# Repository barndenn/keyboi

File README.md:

# MacroPad Concept 
This is my experimental Macropad to test certain features before scaling up. 

Features Included: 
- USB Type-C Connector 
- Bluetooth 
- Battery holder and onboard charging circuit
- OLED Battery Level Display
- Volume Knobs

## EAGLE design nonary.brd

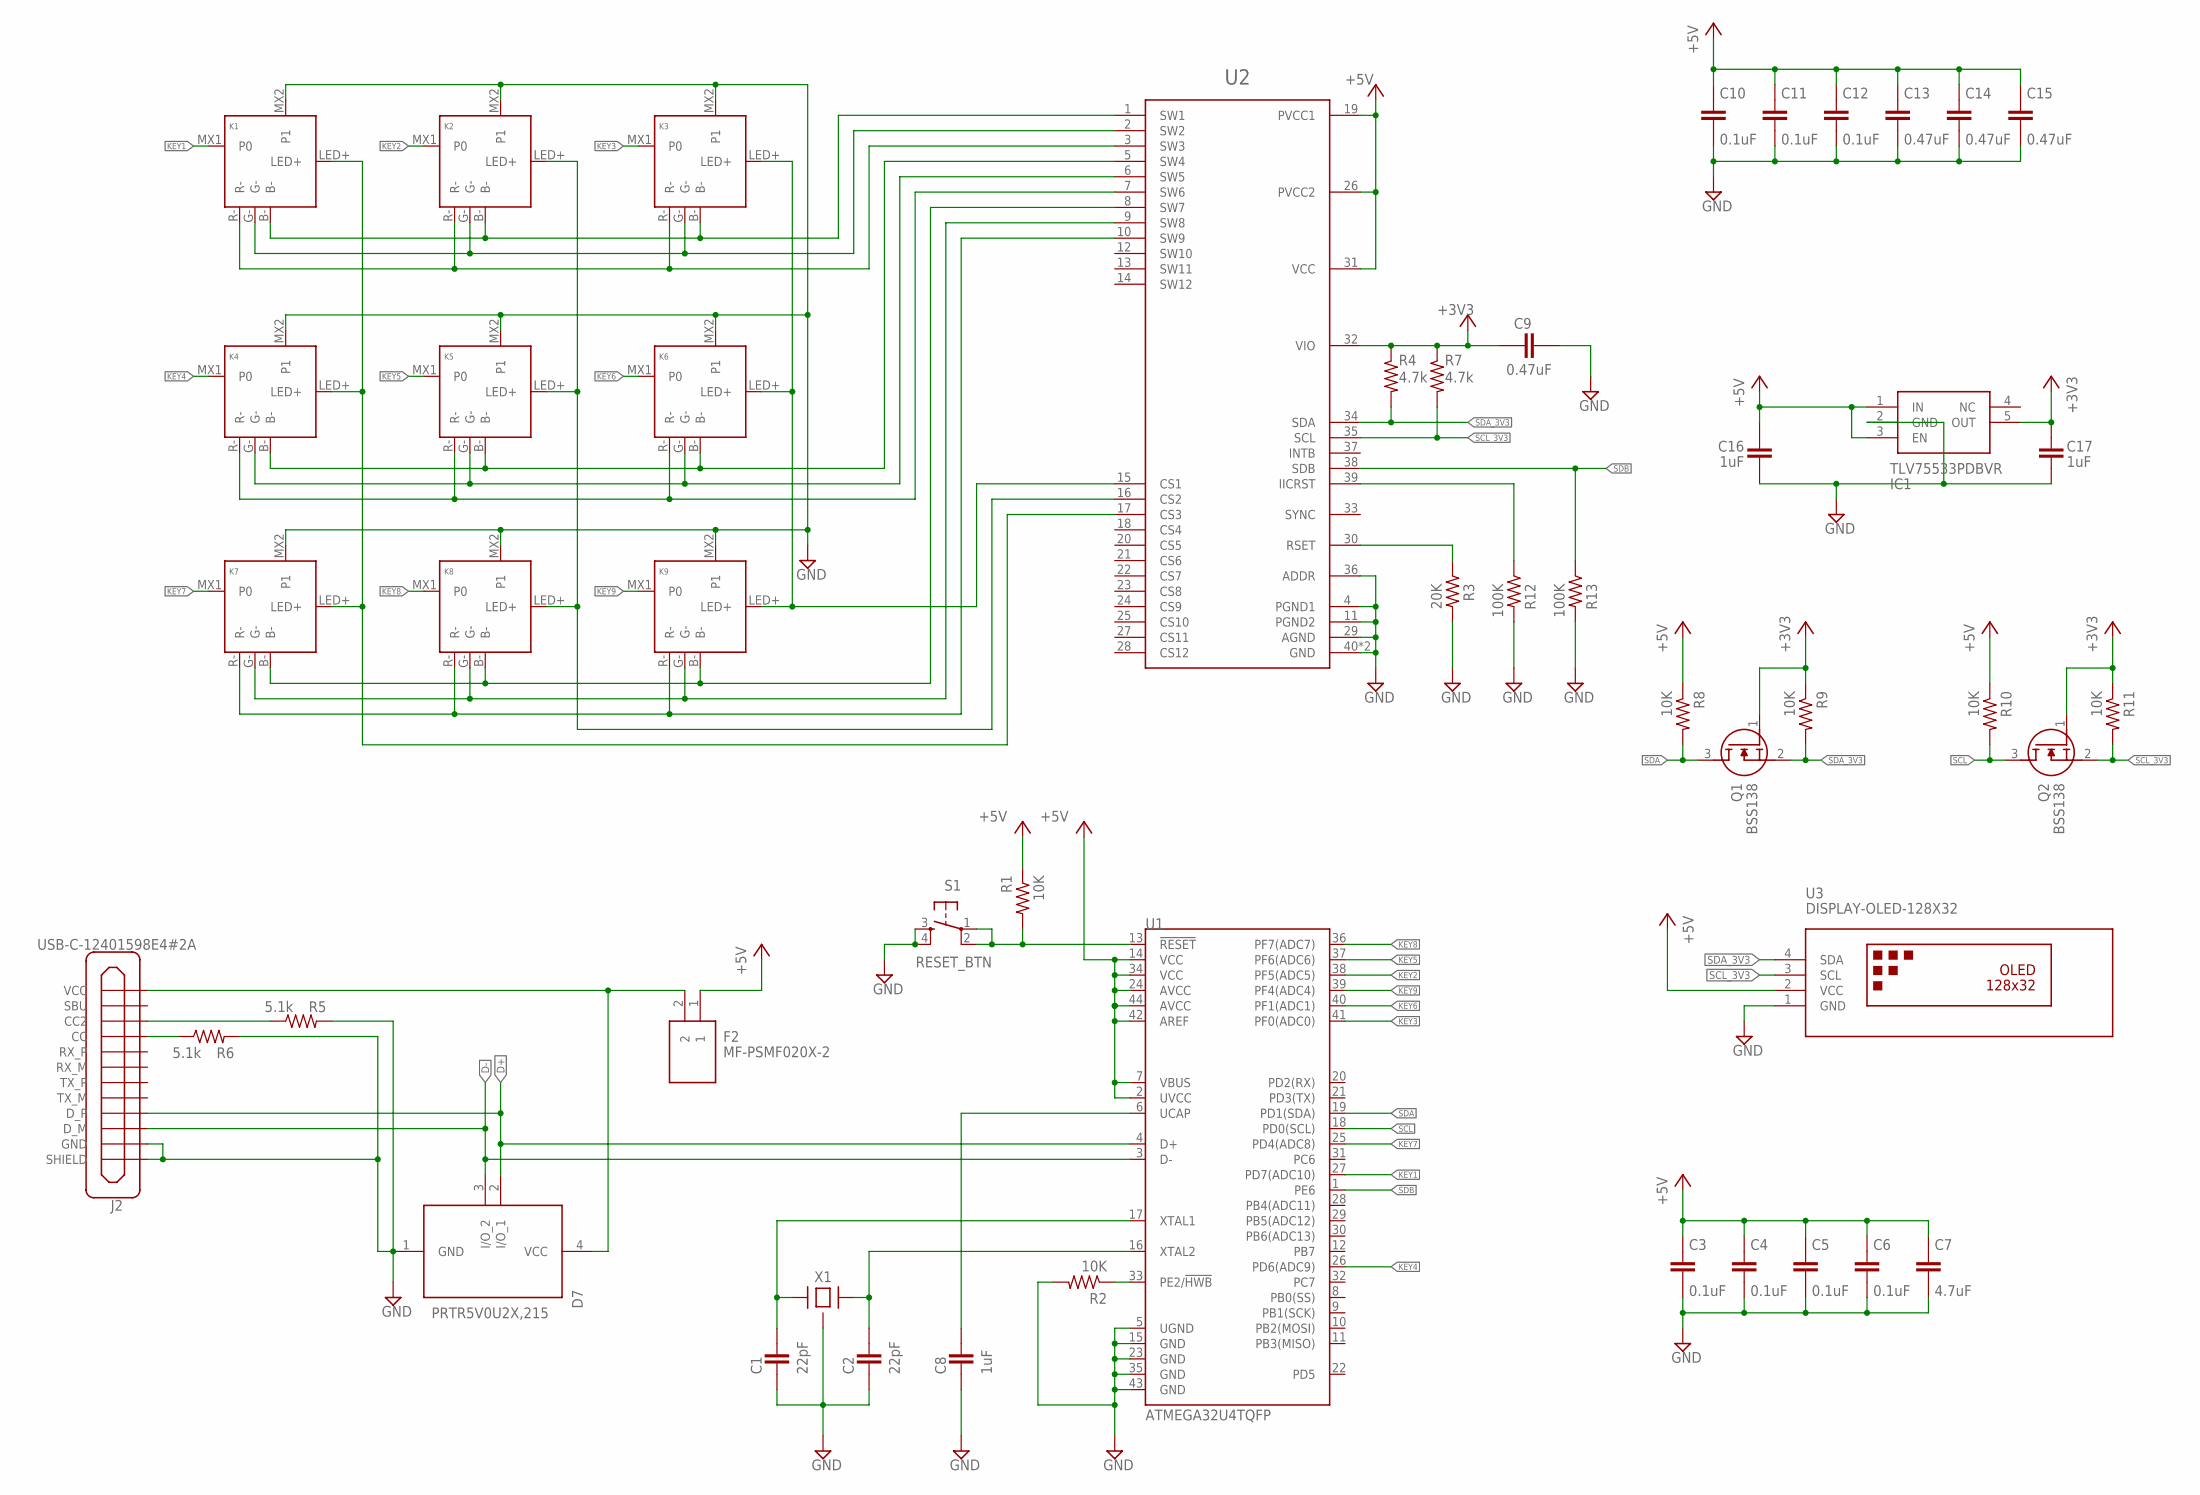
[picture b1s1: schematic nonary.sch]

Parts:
C1, C2: 22pF; C0603
C3, C4, C5, C6, C10, C11, C12: 0.1uF; C0603
C7: 4.7uF; C0603
C8, C16, C17: 1uF; C0603
C9, C13, C14, C15: 0.47uF; C0603
D7: PRTR5V0U2X,215; SOT-143B
F2: MF-PSMF020X-2; FUSC2214X85N
IC1: TLV75533PDBVR; SOT95P280X145-5N
J2: USB-C-12401598E4#2A; 12401598E4#2A
K1, K2, K3, K4, K5, K6, K7, K8, K9: KEYSWITCH-RGBSMDLED-MXHSPCB-1U-SMDRGB; MXHSPCB-1U-SMDRGB
Q1, Q2: BSS138; SOT95P240X120-3N
R1, R2, R8, R9, R10, R11: 10K; R0603
R3: 20K; R0603
R4, R7: 4.7k; R0603
R5, R6: 5.1k; R0603
R12, R13: 100K; R0603
S1: RESET_BTN; TACTILE-SWITCH-SMD
U1: ATMEGA32U4TQFP; SPARKFUN-DIGITALIC_TQFP44
U2: IS31FL3737; QFN-40
U3: DISPLAY-OLED-128X32
X1: CRYSTAL-4PIN-3.2X2.5; CRYSTAL-3.2X2.5

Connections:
+3V3: C9.1, C17.2, IC1.5 (OUT), Q1.1 (G), Q2.1 (G), R4.1, R7.1, R9.1, R11.1, U2.32 (VIO)
+5V: C3.2, C4.2, C5.2, C6.2, C7.2, C10.2, C11.2, C12.2, C13.2, C14.2, C15.2, C16.2, F2.1, IC1.1 (IN), IC1.3 (EN), R1.1, R8.1, R10.1, U1.2 (UVCC), U1.7 (VBUS), U1.14 (VCC), U1.24 (AVCC), U1.34 (VCC), U1.42 (AREF), U1.44 (AVCC), U2.19 (PVCC1), U2.26 (PVCC2), U2.31 (VCC), U3.2 (VCC)
/RESET: R1.2, S1.1, S1.2, U1.13 (!RESET)
CS1: K3.LED+, K6.LED+, K9.LED+, U2.15 (CS1)
CS2: K2.LED+, K5.LED+, K8.LED+, U2.16 (CS2)
CS3: K1.LED+, K4.LED+, K7.LED+, U2.17 (CS3)
D+: D7.2 (I/O_1), J2.A6 (D_P), J2.B6 (D_P), U1.4 (D+)
D-: D7.3 (I/O_2), J2.A7 (D_M), J2.B7 (D_M), U1.3 (D-)
GND: C1.1, C2.1, C3.1, C4.1, C5.1, C6.1, C7.1, C8.1, C9.2, C10.1, C11.1, C12.1, C13.1, C14.1, C15.1, C16.1, C17.1, D7.1 (GND), IC1.2 (GND), J2.A1 (GND), J2.A12 (GND), J2.B1 (GND), J2.B12 (GND), J2.SHIELD@1 (SHIELD), J2.SHIELD@2 (SHIELD), J2.SHIELD@3 (SHIELD), J2.SHIELD@4 (SHIELD), K1.MX2 (P1), K2.MX2 (P1), K3.MX2 (P1), K4.MX2 (P1), K5.MX2 (P1), K6.MX2 (P1), K7.MX2 (P1), K8.MX2 (P1), K9.MX2 (P1), R2.2, R3.2, R5.2, R6.2, R12.2, R13.2, S1.3, S1.4, U1.5 (UGND), U1.15 (GND), U1.23 (GND), U1.35 (GND), U1.43 (GND), U2.4 (PGND1), U2.11 (PGND2), U2.29 (AGND), U2.36 (ADDR), U2.40 (GND), U2.TAB (GND), U3.1 (GND), X1.2 (GND), X1.4 (GND)
KEY1: K1.MX1 (P0), U1.27 (PD7(ADC10))
KEY2: K2.MX1 (P0), U1.38 (PF5(ADC5))
KEY3: K3.MX1 (P0), U1.41 (PF0(ADC0))
KEY4: K4.MX1 (P0), U1.26 (PD6(ADC9))
KEY5: K5.MX1 (P0), U1.37 (PF6(ADC6))
KEY6: K6.MX1 (P0), U1.40 (PF1(ADC1))
KEY7: K7.MX1 (P0), U1.25 (PD4(ADC8))
KEY8: K8.MX1 (P0), U1.36 (PF7(ADC7))
KEY9: K9.MX1 (P0), U1.39 (PF4(ADC4))
unnamed: R12.1, U2.39 (IICRST)
unnamed: R3.1, U2.30 (RSET)
unnamed: J2.A5 (CC), R6.1
unnamed: R2.1, U1.33 (PE2/!HWB)
unnamed: C8.2, U1.6 (UCAP)
unnamed: J2.B5 (CC2), R5.1
unnamed: D7.4 (VCC), F2.2, J2.A4 (VCC), J2.A9 (VCC), J2.B4 (VCC), J2.B9 (VCC)
SCL: Q2.3 (D), R10.2, U1.18 (PD0(SCL))
SCL_3V3: Q2.2 (S), R7.2, R11.2, U2.35 (SCL), U3.3 (SCL)
SDA: Q1.3 (D), R8.2, U1.19 (PD1(SDA))
SDA_3V3: Q1.2 (S), R4.2, R9.2, U2.34 (SDA), U3.4 (SDA)
SDB: R13.1, U1.1 (PE6), U2.38 (SDB)
SW1: K1.B-, K2.B-, K3.B-, U2.1 (SW1)
SW2: K1.G-, K2.G-, K3.G-, U2.2 (SW2)
SW3: K1.R-, K2.R-, K3.R-, U2.3 (SW3)
SW4: K4.B-, K5.B-, K6.B-, U2.5 (SW4)
SW5: K4.G-, K5.G-, K6.G-, U2.6 (SW5)
SW6: K4.R-, K5.R-, K6.R-, U2.7 (SW6)
SW7: K7.B-, K8.B-, K9.B-, U2.8 (SW7)
SW8: K7.G-, K8.G-, K9.G-, U2.9 (SW8)
SW9: K7.R-, K8.R-, K9.R-, U2.10 (SW9)
XTAL1: C1.2, U1.17 (XTAL1), X1.1
XTAL2: C2.2, U1.16 (XTAL2), X1.3 (2)

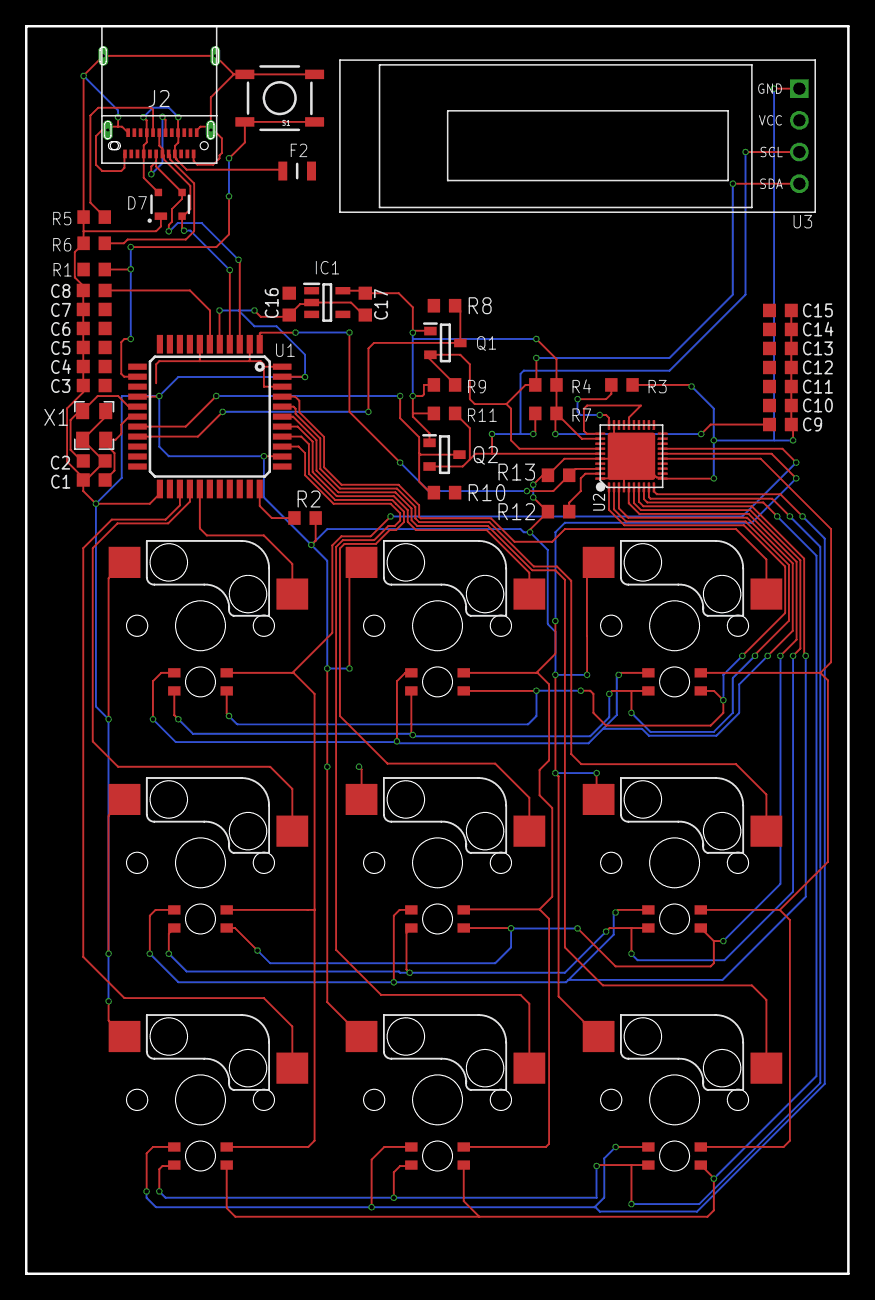
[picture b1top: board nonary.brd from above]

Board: 2 copper layers, 65.9 x 100.0 mm, 50 parts (0 on the bottom side), 41 nets.

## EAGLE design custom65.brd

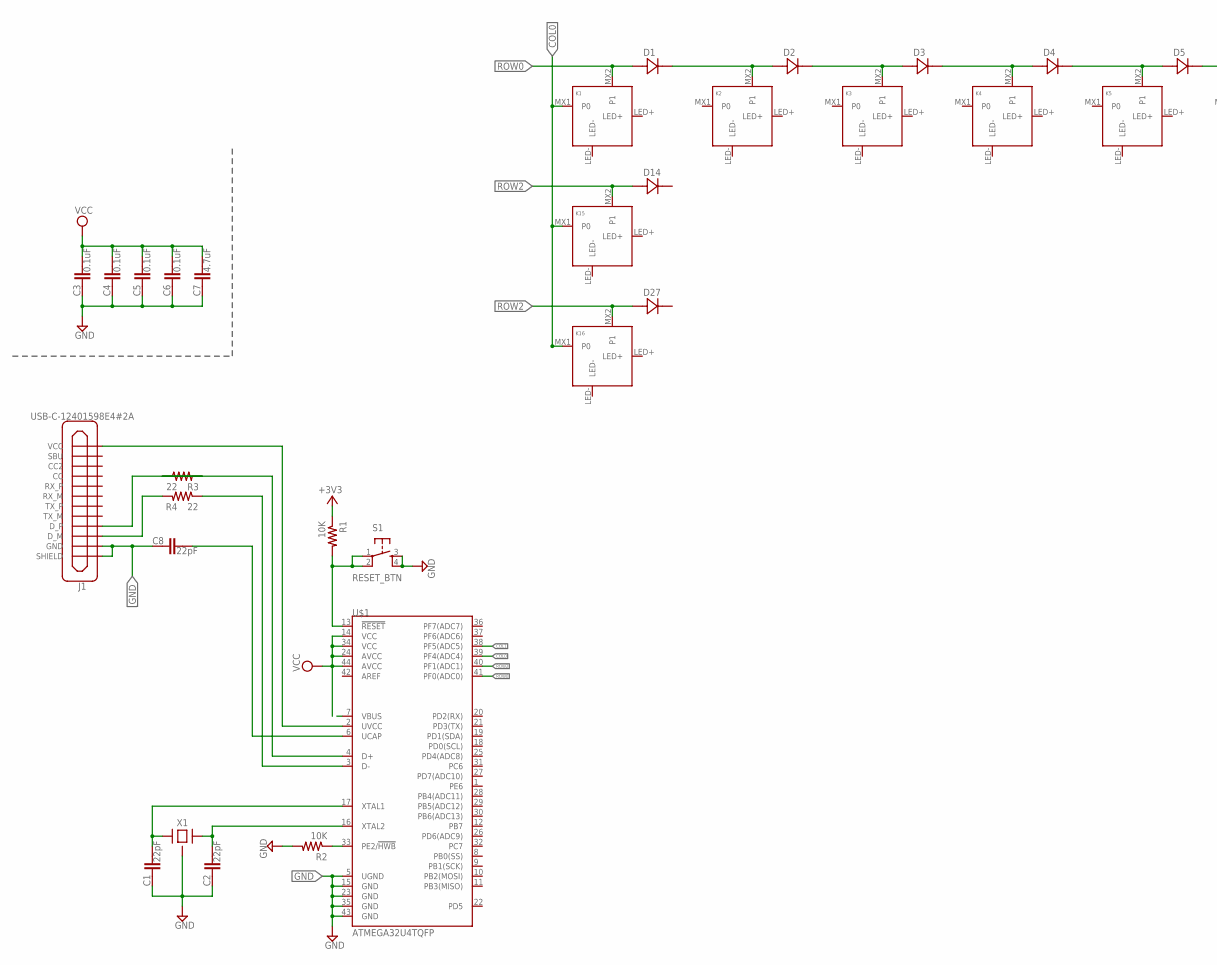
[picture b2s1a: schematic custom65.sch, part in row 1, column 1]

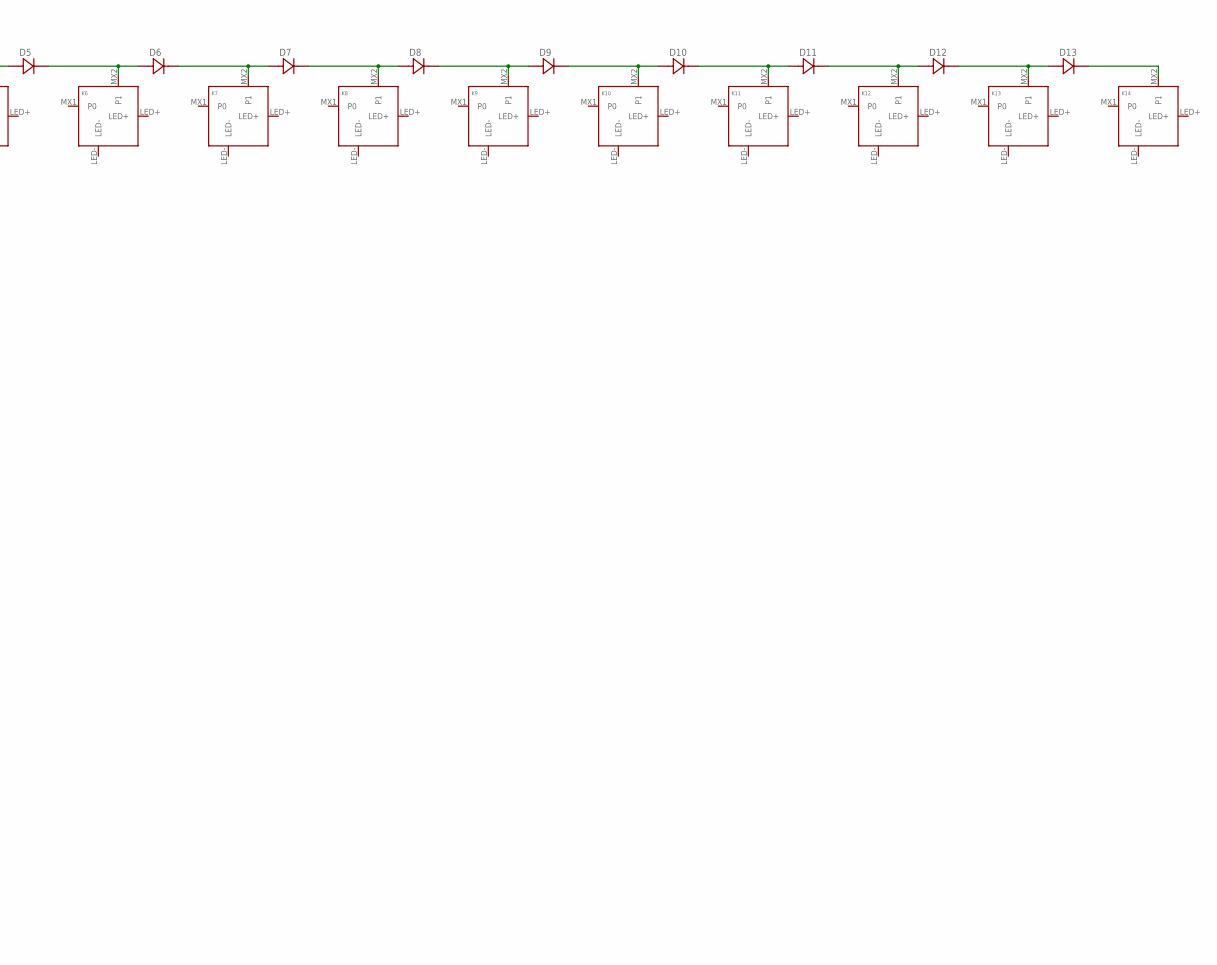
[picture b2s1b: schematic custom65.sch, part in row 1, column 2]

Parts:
C1, C2, C8: 22pF; C0603
C3, C4, C5, C6: 0.1uF; C0603
C7: 4.7uF; C0603
D1, D2, D3, D4, D5, D6, D7, D8, D9, D10, D11, D12, D13, D14, D27: DIODE-DFN0603-2; DFN0603-2
J1: USB-C-12401598E4#2A; 12401598E4#2A
K1, K2, K3, K4, K5, K6, K7, K8, K9, K10, K11, K12, K13, K14, K15, K16: KEYSWITCH-LEDTHTHOLE-MXHS-1U-LEDTHTHOLE; MXHS-1U-LEDTHTHOLE
R1, R2: 10K; R0603
R3, R4: 22; R0603
S1: RESET_BTN; TACTILE-SWITCH-SMD
U$1: ATMEGA32U4TQFP; SPARKFUN-DIGITALIC_TQFP44
X1: CRYSTAL-4PIN-3.2X2.5; CRYSTAL-3.2X2.5

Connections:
+3V3: R1.1
COL0: K1.MX1 (P0), K15.MX1 (P0), K16.MX1 (P0), U$1.39 (PF4(ADC4))
COL1: U$1.38 (PF5(ADC5))
GND: C1.1, C2.1, C3.1, C4.1, C5.1, C6.1, C7.1, C8.1, J1.A1 (GND), J1.A12 (GND), J1.B1 (GND), J1.B12 (GND), J1.SHIELD@1 (SHIELD), J1.SHIELD@2 (SHIELD), J1.SHIELD@3 (SHIELD), J1.SHIELD@4 (SHIELD), R2.2, S1.3, S1.4, U$1.5 (UGND), U$1.15 (GND), U$1.23 (GND), U$1.35 (GND), U$1.43 (GND), X1.2 (GND), X1.4 (GND)
unnamed: C1.2, U$1.17 (XTAL1), X1.1
unnamed: C2.2, U$1.16 (XTAL2), X1.3 (2)
unnamed: R1.2, S1.1, S1.2, U$1.13 (!RESET)
unnamed: R2.1, U$1.33 (PE2/!HWB)
unnamed: C8.2, U$1.6 (UCAP)
unnamed: J1.A4 (VCC), J1.A9 (VCC), J1.B4 (VCC), J1.B9 (VCC), U$1.2 (UVCC)
unnamed: J1.A6 (D_P), J1.B6 (D_P), R3.2
unnamed: R3.1, U$1.4 (D+)
unnamed: R4.1, U$1.3 (D-)
unnamed: J1.A7 (D_M), J1.B7 (D_M), R4.2
unnamed: D2.C, D3.A, K3.MX2 (P1)
unnamed: D3.C, D4.A, K4.MX2 (P1)
unnamed: D1.C, D2.A, K2.MX2 (P1)
unnamed: D4.C, D5.A, K5.MX2 (P1)
unnamed: D5.C, D6.A, K6.MX2 (P1)
unnamed: D6.C, D7.A, K7.MX2 (P1)
unnamed: D7.C, D8.A, K8.MX2 (P1)
unnamed: D8.C, D9.A, K9.MX2 (P1)
unnamed: D9.C, D10.A, K10.MX2 (P1)
unnamed: D10.C, D11.A, K11.MX2 (P1)
unnamed: D11.C, D12.A, K12.MX2 (P1)
unnamed: D12.C, D13.A, K13.MX2 (P1)
unnamed: D13.C, K14.MX2 (P1)
ROW0: D1.A, K1.MX2 (P1), U$1.41 (PF0(ADC0))
ROW2: D14.A, D27.A, K15.MX2 (P1), K16.MX2 (P1), U$1.40 (PF1(ADC1))
VCC: C3.2, C4.2, C5.2, C6.2, C7.2, U$1.7 (VBUS), U$1.14 (VCC), U$1.24 (AVCC), U$1.34 (VCC), U$1.44 (AVCC)

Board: 2 copper layers, 47 parts (0 on the bottom side), 28 nets, no tracks yet.

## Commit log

2019-06-01 started designing custom keyboard
2019-06-01 added eagle libraries
2019-06-01 updating readme.md
2019-06-09 updated sch and brd files
2020-01-02 updated file names
2020-01-03 Made modifications to the keyboard.lbr, brd, and sch files
2020-01-04 Routing on the Board
2020-01-05 New Libraries and finished board/schematic
2020-01-05 removed a USB Type-C lbr file

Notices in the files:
parts and their libraries:
SparkFun-Retired: Licensing: Creative Commons ShareAlike 4.0 International - https://creativecommons.org/licenses/by-sa/4.0
diy-modules: Released under the Creative Commons Attribution 4.0 International License: http://creativecommons.org/licenses/by/4.0
